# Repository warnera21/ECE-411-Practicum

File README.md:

# ECE-411-Practicum
Practicum Project

Preliminary Schematic -
Will be trying to get an I2C connection for LCD so to not take up so many connections.
Need to improve the layout, was transferred from another program.

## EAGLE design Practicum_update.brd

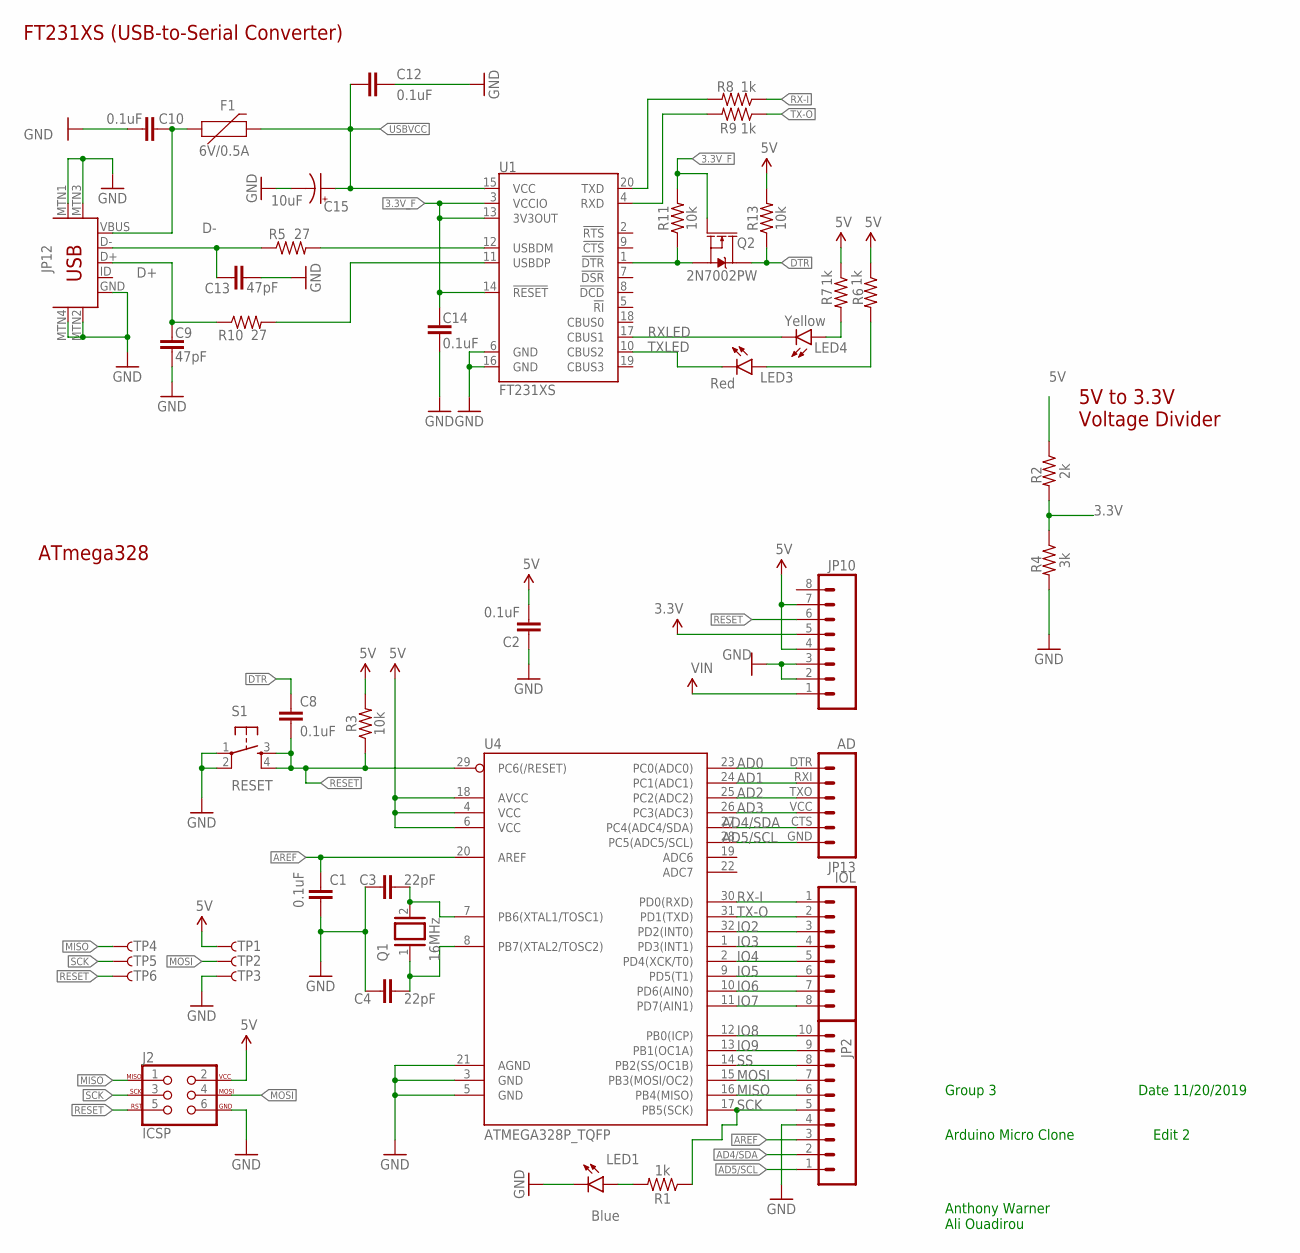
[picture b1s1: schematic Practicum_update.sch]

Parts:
C1, C2, C8, C10, C12, C14: 0.1uF; 0603
C3, C4: 22pF; 0603
C9, C13: 47pF; 0603
C15: 10uF; EIA3216
F1: 6V/0.5A; 1206
J2: ICSP; 2X3-NS
JP2: M10"; 1X10
JP10: M081X08; 1X08
JP11: IOL; 1X08
JP12: USB-MINIB-5PIN; USB-MINIB
JP13: AD; 1X06
LED1: Blue; LED-1206
LED3: Red; LED-1206
LED4: Yellow; LED-1206
Q1: 16MHz; QS
Q2: 2N7002PW; SOT323
R1, R6, R7, R8, R9: 1k; 0603
R2: 2k; 0603
R3, R11, R13: 10k; 0603
R4: 3k; 0603
R5, R10: 27; 0603
S1: RESET; TACTILE-SWITCH-SMD
TP1, TP2, TP3, TP4, TP5, TP6: TP-3x5; PAD.03X.05
U1: FT231XS; SSOP20_L
U4: ATMEGA328P_TQFP; TQFP32-08

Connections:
3.3V: JP10.5, R2.2, R4.1
3.3V_F: C14.1, Q2.1 (G), R11.2, U1.3 (VCCIO), U1.13 (3V3OUT), U1.14 (!RESET)
5V: C2.2, J2.2, JP10.4, JP10.7, R2.1, R3.2, R6.1, R7.1, R13.2, TP1.P$1, U4.4 (VCC), U4.6 (VCC), U4.18 (AVCC)
AD0: JP13.DTR (1), U4.23 (PC0(ADC0))
AD1: JP13.RXI (2), U4.24 (PC1(ADC1))
AD2: JP13.TXO (3), U4.25 (PC2(ADC2))
AD3: JP13.VCC (4), U4.26 (PC3(ADC3))
AD4/SDA: JP2.2, JP13.CTS (5), U4.27 (PC4(ADC4/SDA))
AD5/SCL: JP2.1, JP13.GND (6), U4.28 (PC5(ADC5/SCL))
AREF: C1.1, JP2.3, U4.20 (AREF)
D+: C9.1, JP12.D+, R10.1
D-: C13.1, JP12.D-, R5.1
DTR: C8.1, Q2.3 (D), R13.1
FTDI_DTR: Q2.2 (S), R11.1, U1.1 (!DTR)
GND: C1.2, C2.1, C3.1, C4.1, C9.2, C10.2, C12.2, C13.2, C14.2, C15.-, J2.6, JP2.4, JP10.2, JP10.3, JP12.GND, JP12.MTN1 (MTN2), JP12.MTN2 (MTN3), JP12.MTN3 (MTN1), JP12.MTN4, LED1.C, R4.2, S1.1, S1.2, TP3.P$1, U1.6 (GND), U1.16 (GND), U4.3 (GND), U4.5 (GND), U4.21 (AGND)
IO2: JP11.3, U4.32 (PD2(INT0))
IO3: JP11.4, U4.1 (PD3(INT1))
IO4: JP11.5, U4.2 (PD4(XCK/T0))
IO5: JP11.6, U4.9 (PD5(T1))
IO6: JP11.7, U4.10 (PD6(AIN0))
IO7: JP11.8, U4.11 (PD7(AIN1))
IO8: JP2.10, U4.12 (PB0(ICP))
IO9: JP2.9, U4.13 (PB1(OC1A))
MISO: J2.1, JP2.6, TP4.P$1, U4.16 (PB4(MISO))
MOSI: J2.4, JP2.7, TP2.P$1, U4.15 (PB3(MOSI/OC2))
unnamed: LED1.A, R1.2
unnamed: C4.2, Q1.1, U4.8 (PB7(XTAL2/TOSC2))
unnamed: C3.2, Q1.2, U4.7 (PB6(XTAL1/TOSC1))
unnamed: R10.2, U1.11 (USBDP)
unnamed: R5.2, U1.12 (USBDM)
unnamed: LED3.A, R6.2
unnamed: LED4.A, R7.2
RESET: C8.2, J2.5, JP10.6, R3.1, S1.3, S1.4, TP6.P$1, U4.29 (PC6(/RESET))
RX-I: JP11.1, R8.1, U4.30 (PD0(RXD))
RXD: R9.2, U1.4 (RXD)
RXLED: LED4.C, U1.17 (CBUS1)
SCK: J2.3, JP2.5, R1.1, TP5.P$1, U4.17 (PB5(SCK))
SS: JP2.8, U4.14 (PB2(SS/OC1B))
TX-O: JP11.2, R9.1, U4.31 (PD1(TXD))
TXD: R8.2, U1.20 (TXD)
TXLED: LED3.C, U1.10 (CBUS2)
USBVCC: C12.1, C15.+, F1.2, U1.15 (VCC)
VIN: JP10.1
VUSB: C10.1, F1.1, JP12.VBUS

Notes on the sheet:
ATmega328
FT231XS (USB-to-Serial Converter)
Group 3
Arduino Micro Clone
Anthony Warner Ali Ouadirou
Edit 2
Date 11/20/2019
5V to 3.3V Voltage Divider

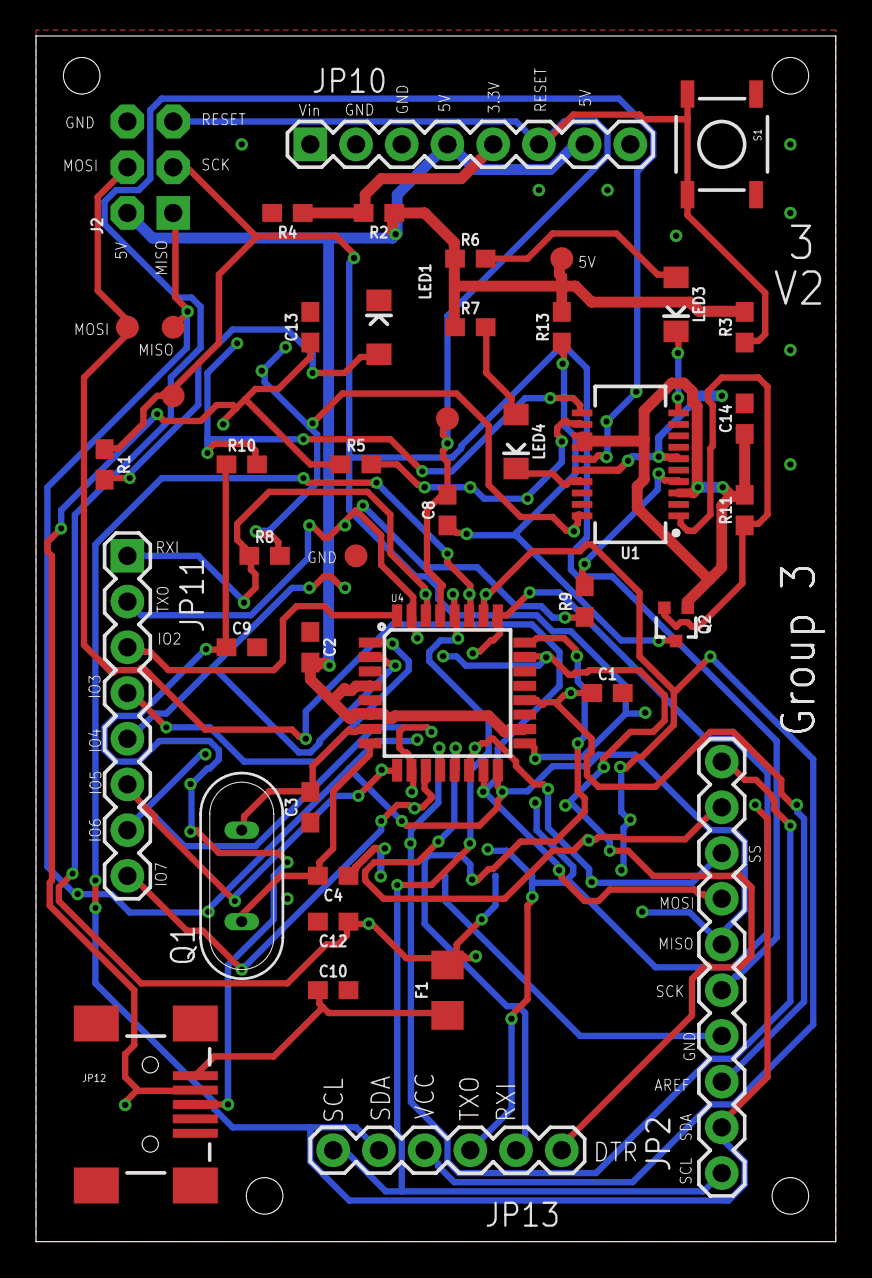
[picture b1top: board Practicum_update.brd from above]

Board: 2 copper layers, 44.4 x 67.0 mm, 44 parts (1 on the bottom side), 43 nets.

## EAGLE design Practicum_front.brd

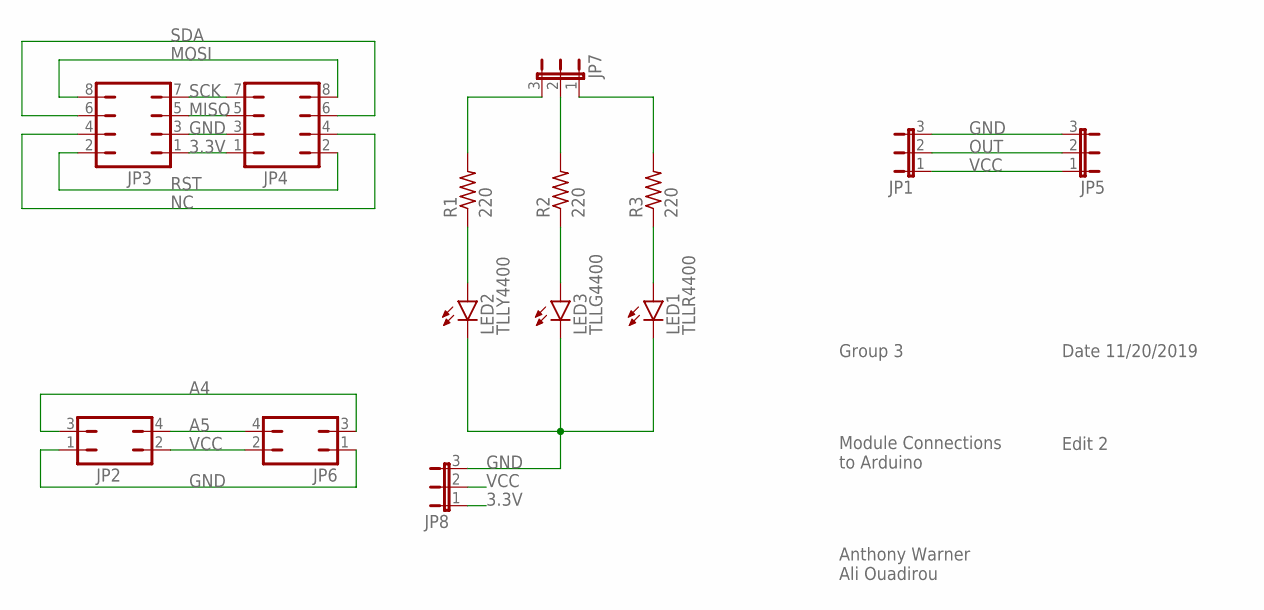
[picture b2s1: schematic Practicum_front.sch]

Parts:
JP1, JP5, JP7, JP8: 0; JP2
JP2, JP6: 0; JP2Q
JP3, JP4: 0; JP4Q
LED1: TLLR4400; LED3MM
LED2: TLLY4400; LED3MM
LED3: TLLG4400; LED3MM
R1, R2, R3: 220; M0805

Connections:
3.3V: JP3.1, JP4.1, JP8.1
A4: JP2.3, JP6.3
A5: JP2.4, JP6.4
GND: JP1.3, JP2.1, JP3.3, JP4.3, JP5.3, JP6.1, JP8.3, LED1.K (C), LED2.K (C), LED3.K (C)
MISO: JP3.5, JP4.5
MOSI: JP3.8, JP4.8
unnamed: JP7.3, R1.2
unnamed: JP7.2, R2.2
unnamed: LED1.A, R3.1
unnamed: LED3.A, R2.1
unnamed: LED2.A, R1.1
unnamed: JP7.1, R3.2
NC: JP3.4, JP4.4
OUT: JP1.2, JP5.2
RST: JP3.2, JP4.2
SCK: JP3.7, JP4.7
SDA: JP3.6, JP4.6
VCC: JP1.1, JP2.2, JP5.1, JP6.2, JP8.2

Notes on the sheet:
Group 3
Date 11/20/2019
Edit 2
Module Connections to Arduino
Anthony Warner Ali Ouadirou

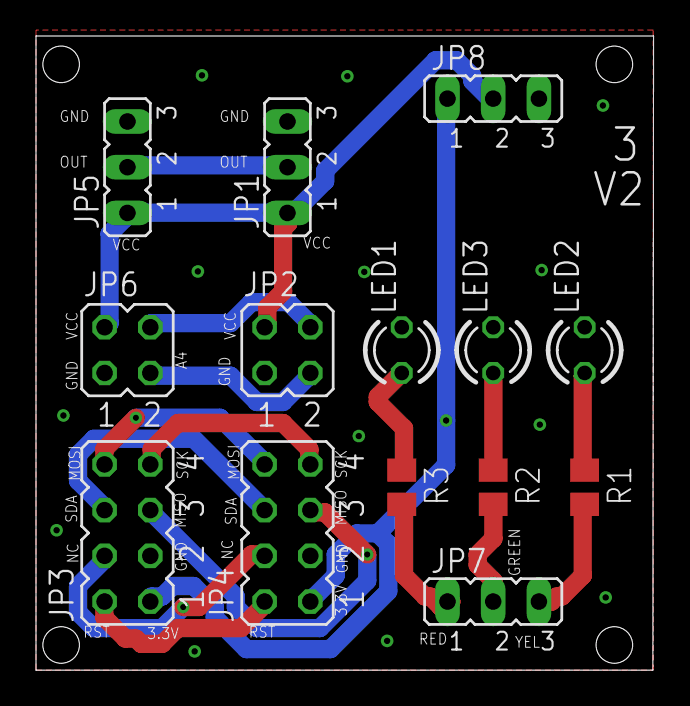
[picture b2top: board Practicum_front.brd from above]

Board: 2 copper layers, 34.3 x 35.2 mm, 14 parts (0 on the bottom side), 18 nets.

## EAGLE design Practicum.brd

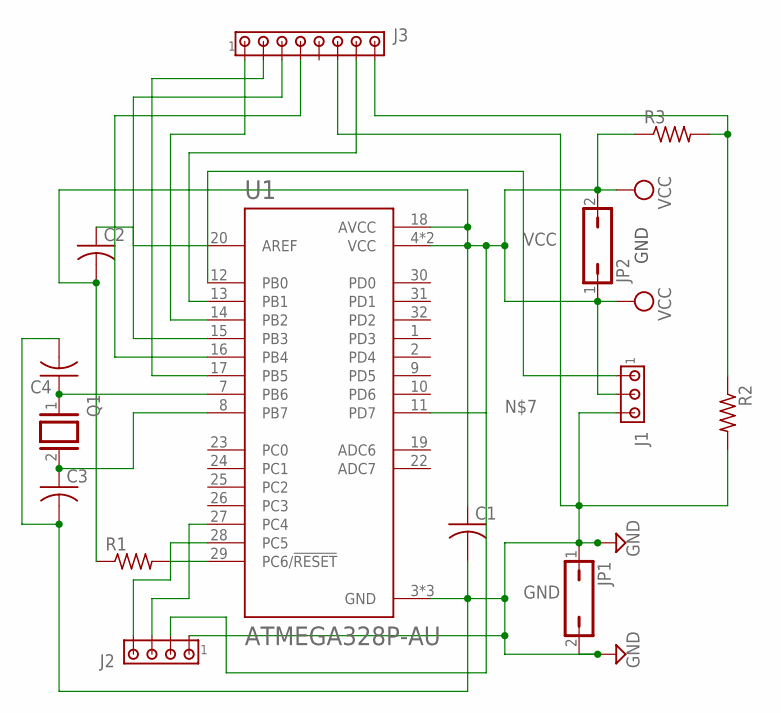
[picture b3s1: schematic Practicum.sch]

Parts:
C1, C2, C3, C4: C-USC0603; C0603
J1: MTA03-100; 10X03MTA
J2: MTA04-100; 10X04MTA
J3: MTA08-100; 10X08MTA
JP1, JP2: JP1Q; JP1
Q1: XTAL/S; QS
R1, R2, R3: R-US_R0603; R0603
U1: ATMEGA328P-AU; QFP80P900X900X120-32N

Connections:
GND: C1.2, C3.2, C4.2, J1.3, J2.1, J3.6, JP1.1, JP1.2, R2.2, U1.3 (GND), U1.5 (GND), U1.21 (GND)
unnamed: C4.1, Q1.1, U1.7 (PB6)
unnamed: C3.1, Q1.2, U1.8 (PB7)
unnamed: J3.3, U1.15 (PB3)
unnamed: R1.2, U1.29 (PC6/!RESET)
unnamed: J3.4, U1.16 (PB4)
unnamed: C2.1, U1.20 (AREF)
unnamed: J3.7, U1.13 (PB1)
unnamed: J2.3, U1.27 (PC4)
unnamed: J2.4, U1.28 (PC5)
unnamed: J1.1, U1.12 (PB0)
unnamed: J3.1, U1.14 (PB2)
unnamed: J3.8, R2.1, R3.2
unnamed: J3.2, U1.17 (PB5)
VCC: C1.1, C2.2, J1.2, J2.2, JP2.1, JP2.2, R1.1, R3.1, U1.4 (VCC), U1.6 (VCC), U1.18 (AVCC)

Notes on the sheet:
GND

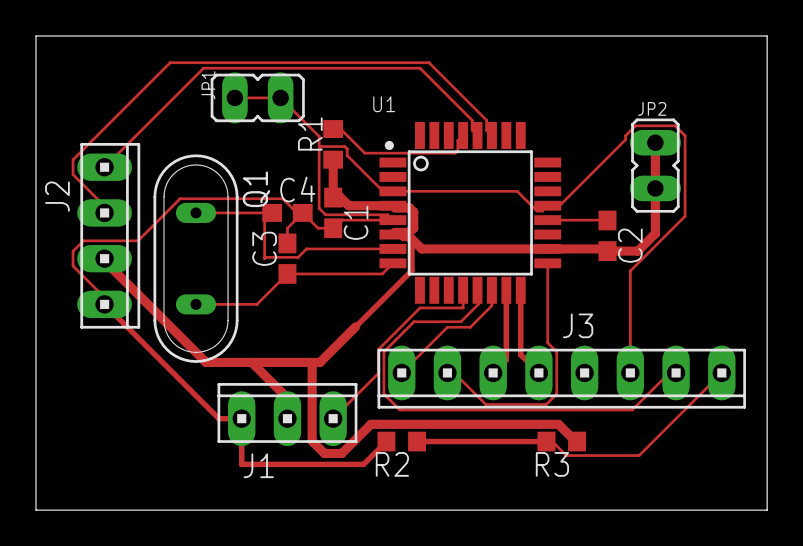
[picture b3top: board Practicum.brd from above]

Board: 2 copper layers, 40.6 x 26.3 mm, 14 parts (0 on the bottom side), 15 nets.

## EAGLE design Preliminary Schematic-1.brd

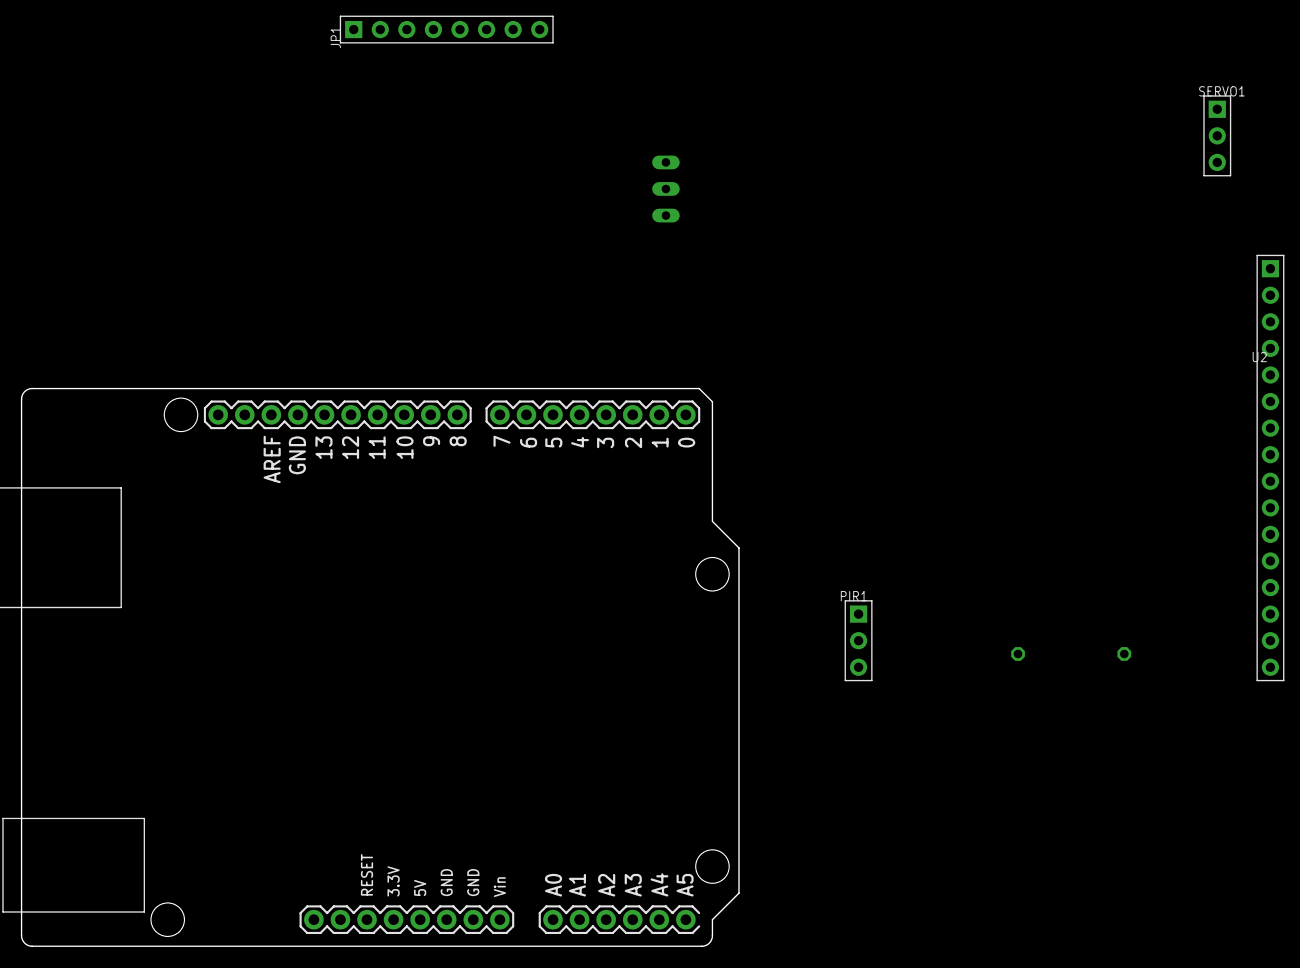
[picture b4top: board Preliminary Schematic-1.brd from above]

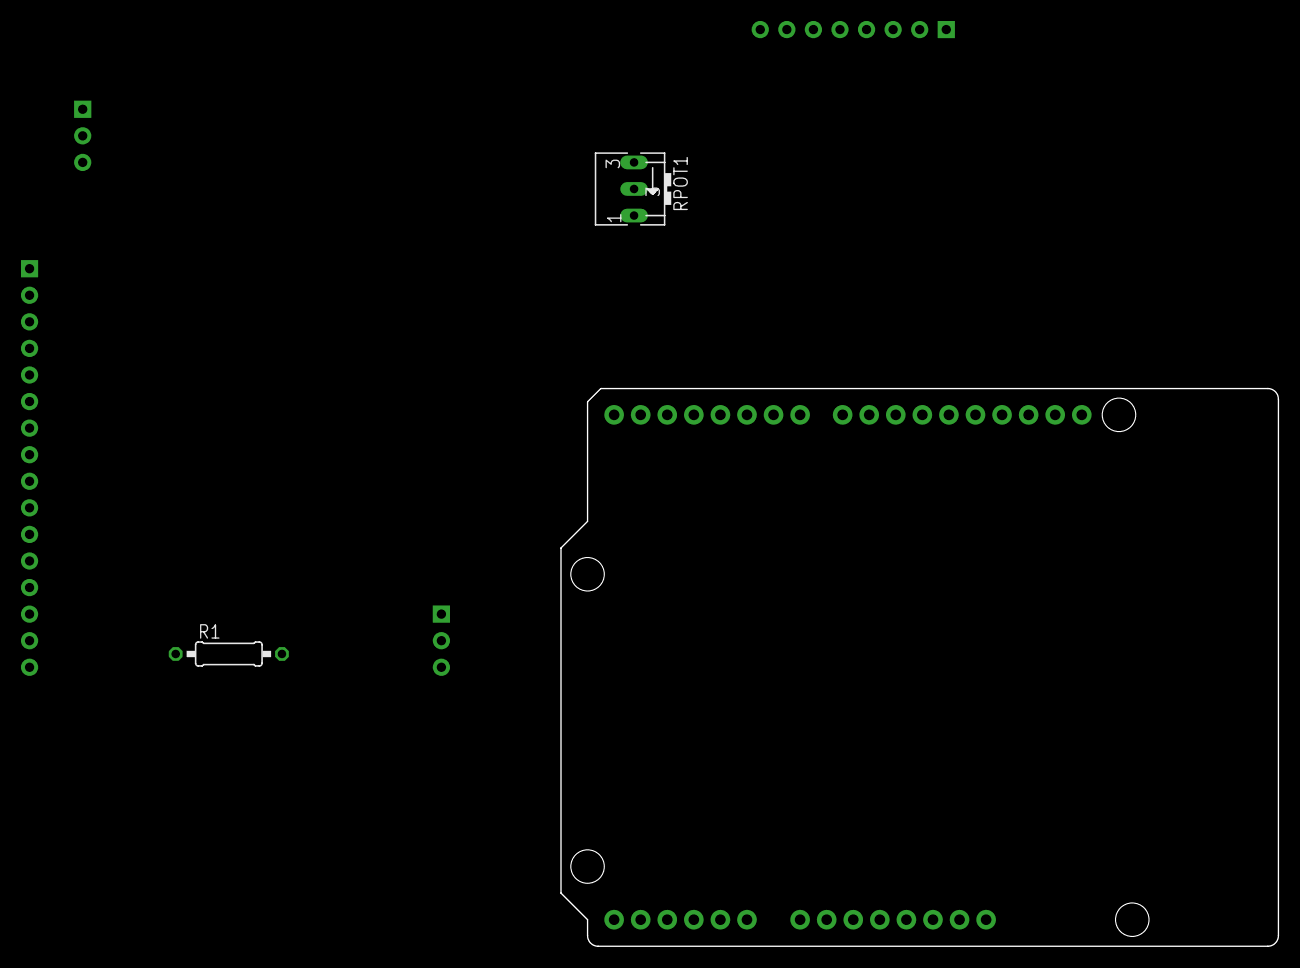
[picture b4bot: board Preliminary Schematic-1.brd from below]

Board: 2 copper layers, 68.6 x 53.3 mm, 7 parts (2 on the bottom side), 20 nets, no tracks yet.

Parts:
JP1: 1X8P-2.54-2.54-11.6-3.0-BLACK-MALE
PIR1: 1X3P-2.54-2.54-11.6-3.0-BLACK-MALE
R1: 220‎Ω; 0207/10
RPOT1: 10k‎Ω; B25V
SERVO1: 1X3P-2.54-2.54-11.6-3.0-BLACK-MALE
U1: ARDUINO_UNO
U2: 1X16P-2.54-2.54-11.6-3.0-BLACK-MALE

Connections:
unnamed: U1.2, U2.6
unnamed: U1.1, U2.4
unnamed: U1.4, U2.11
unnamed: U1.5, U2.12
unnamed: U1.6, U2.13
unnamed: U1.7, U2.14
unnamed: JP1.6, U1.GND, U2.1, U2.5, U2.16
unnamed: PIR1.2, R1.2, RPOT1.E, SERVO1.2, U1.5V, U2.2
unnamed: PIR1.1, SERVO1.1
unnamed: SERVO1.3, U1.3
unnamed: PIR1.3, U1.8
unnamed: RPOT1.S, U2.3
unnamed: RPOT1.A, U1.GND.
unnamed: R1.1, U2.15
unnamed: JP1.1, U1.10
unnamed: JP1.2, U1.13
unnamed: JP1.3, U1.11
unnamed: JP1.4, U1.12
unnamed: JP1.7, U1.9
unnamed: JP1.8, U1.3.3V

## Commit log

2019-10-31 Add files via upload
    Will be trying to get an I2C connection for LCD so to not take up so many connections.
    Need to improve the layout, was transferred from another program.

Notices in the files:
parts and their libraries:
SparkFun-Capacitors: Licensing: CC v3.0 Share-Alike You are welcome to use this library for commercial purposes.
SparkFun-Fuses: Licensing: Creative Commons ShareAlike 4.0 International - https://creativecommons.org/licenses/by-sa/4.0
